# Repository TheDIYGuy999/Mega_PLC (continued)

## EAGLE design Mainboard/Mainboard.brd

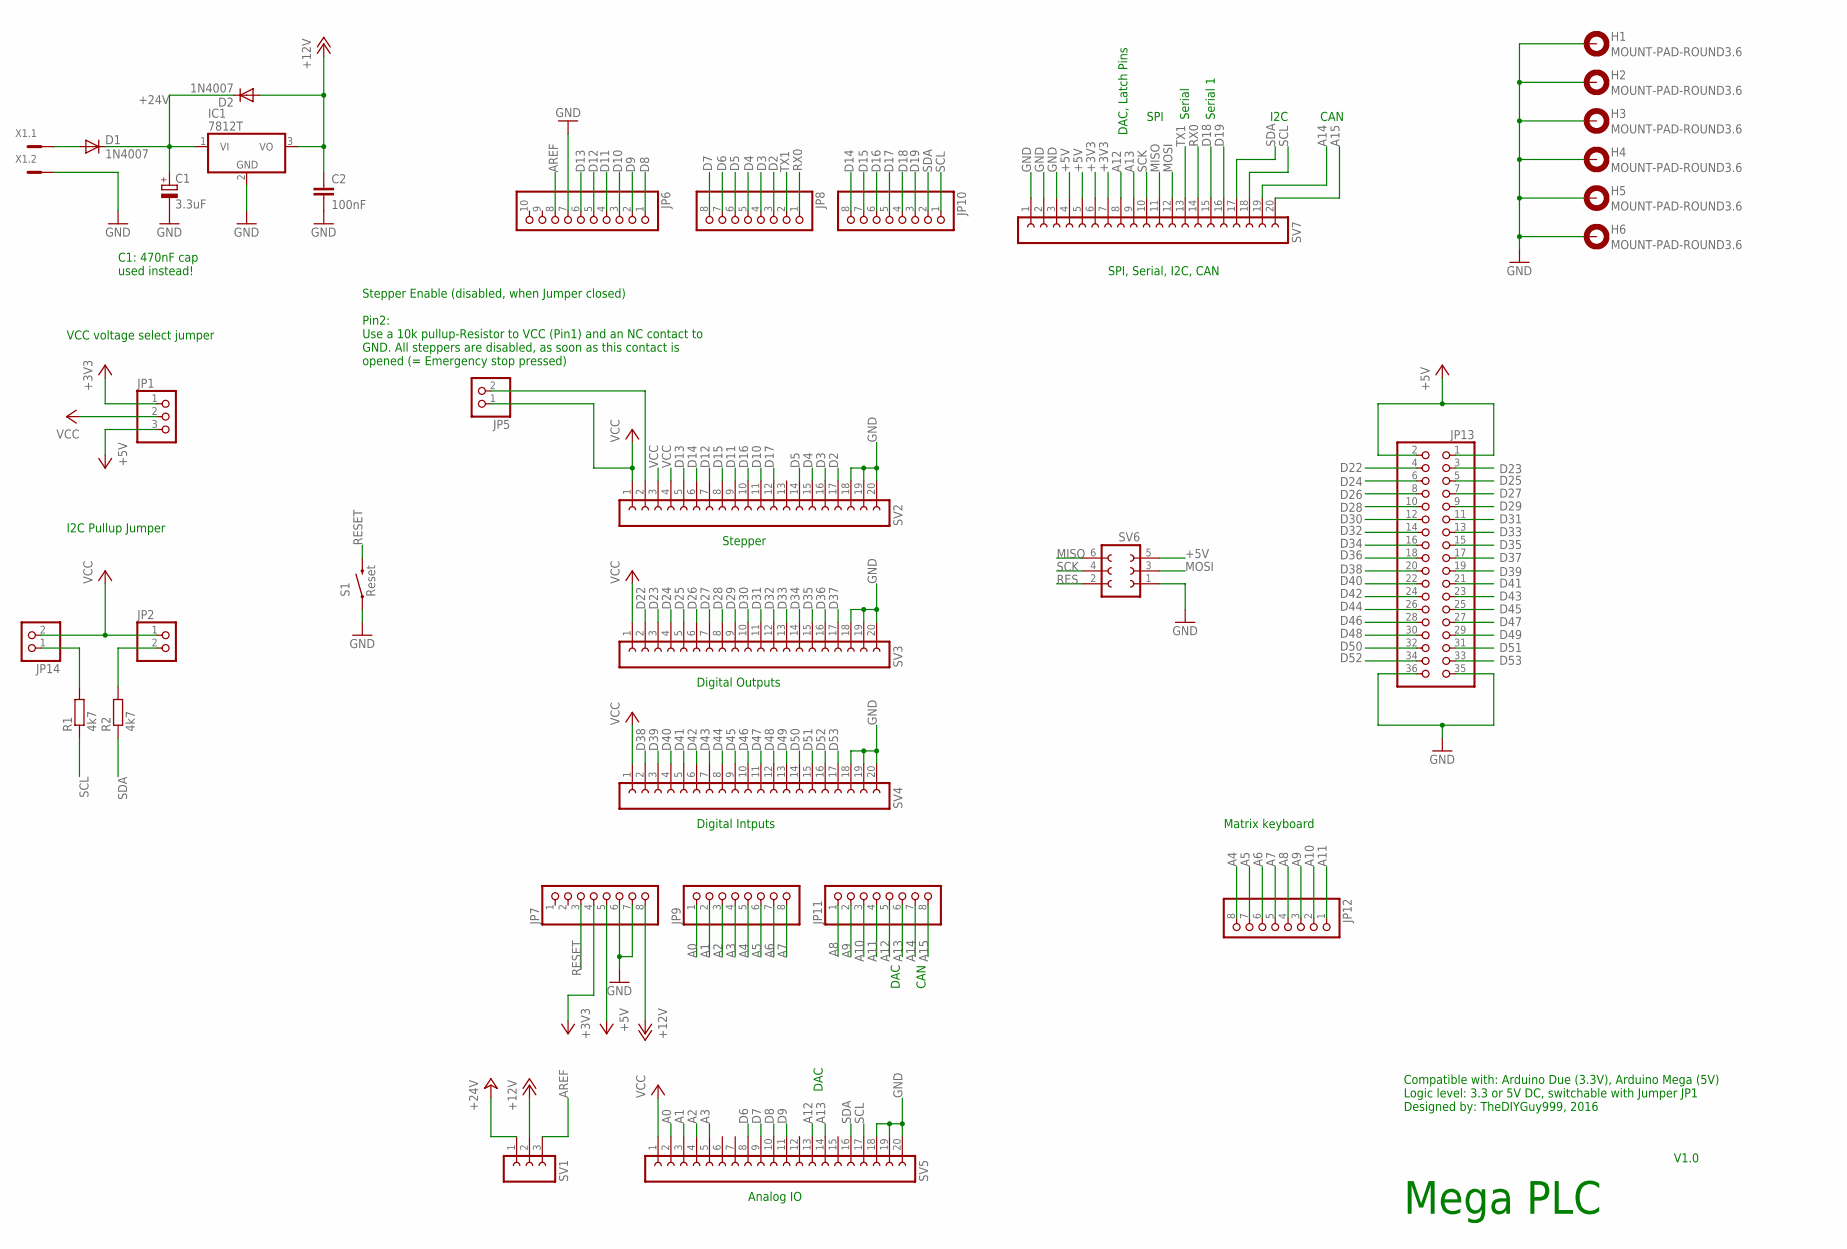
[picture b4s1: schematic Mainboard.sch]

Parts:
C1: 3.3uF; B45181A
C2: 100nF; C025-024X044
D1, D2: 1N4007; DO41-10
H1, H2, H3, H4, H5, H6: MOUNT-PAD-ROUND3.6; 3,6-PAD
IC1: 7812T; TO220H
JP1: PINHD-1X3; 1X03
JP2, JP5, JP14: PINHD-1X2; 1X02
JP6: PINHD-1X10; 1X10
JP7, JP8, JP9, JP10, JP11, JP12: PINHD-1X8; 1X08
JP13: PINHD-2X18; 2X18
R1, R2: 4k7; 0207/10
S1: Reset; TACTILE-PTH
SV1: FE03-1
SV2, SV3, SV4, SV5, SV7: FE20-1; FE20
SV6: FE03-2
X1: MC2

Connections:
+3V3: JP1.1, JP7.4, SV7.6, SV7.7
+5V: JP1.3, JP7.5, JP13.1, JP13.2, SV6.5, SV7.4, SV7.5
+12V: C2.1, D2.A, IC1.3 (VO), JP7.8, SV1.2
+24V: C1.+, D1.C, D2.C, IC1.1 (VI), SV1.1
A0: JP9.1, SV5.2
A1: JP9.2, SV5.3
A2: JP9.3, SV5.4
A3: JP9.4, SV5.5
A4: JP9.5, JP12.8
A5: JP9.6, JP12.7
A6: JP9.7, JP12.6
A7: JP9.8, JP12.5
A8: JP11.1, JP12.4
A9: JP11.2, JP12.3
A10: JP11.3, JP12.2
A11: JP11.4, JP12.1
A12: JP11.5, SV5.13, SV7.8
A13: JP11.6, SV5.14, SV7.9
A14: JP11.7, SV7.19
A15: JP11.8, SV7.20
AREF: JP6.8, SV1.3
D2: JP8.3, SV2.17
D3: JP8.4, SV2.16
D4: JP8.5, SV2.15
D5: JP8.6, SV2.14
D6: JP8.7, SV5.8
D7: JP8.8, SV5.9
D8: JP6.1, SV5.10
D9: JP6.2, SV5.11
D10: JP6.3, SV2.11
D11: JP6.4, SV2.9
D12: JP6.5, SV2.7
D13: JP6.6, SV2.5
D14: JP10.8, SV2.6
D15: JP10.7, SV2.8
D16: JP10.6, SV2.10
D17: JP10.5, SV2.12
D18: JP10.4, SV7.15
D19: JP10.3, SV7.16
D22: JP13.4, SV3.2
D23: JP13.3, SV3.3
D24: JP13.6, SV3.4
D25: JP13.5, SV3.5
D26: JP13.8, SV3.6
D27: JP13.7, SV3.7
D28: JP13.10, SV3.8
D29: JP13.9, SV3.9
D30: JP13.12, SV3.10
D31: JP13.11, SV3.11
D32: JP13.14, SV3.12
D33: JP13.13, SV3.13
D34: JP13.16, SV3.14
D35: JP13.15, SV3.15
D36: JP13.18, SV3.16
D37: JP13.17, SV3.17
D38: JP13.20, SV4.2
D39: JP13.19, SV4.3
D40: JP13.22, SV4.4
D41: JP13.21, SV4.5
D42: JP13.24, SV4.6
D43: JP13.23, SV4.7
D44: JP13.26, SV4.8
D45: JP13.25, SV4.9
D46: JP13.28, SV4.10
D47: JP13.27, SV4.11
D48: JP13.30, SV4.12
D49: JP13.29, SV4.13
D50: JP13.32, SV4.14
D51: JP13.31, SV4.15
D52: JP13.34, SV4.16
D53: JP13.33, SV4.17
GND: C1.-, C2.2, H1.B3,6, H2.B3,6, H3.B3,6, H4.B3,6, H5.B3,6, H6.B3,6, IC1.2 (GND), JP6.7, JP7.6, JP7.7, JP13.35, JP13.36, S1.1, SV2.18, SV2.19, SV2.20, SV3.18, SV3.19, SV3.20, SV4.18, SV4.19, SV4.20, SV5.18, SV5.19, SV5.20, SV6.1, SV7.1, SV7.2, SV7.3, X1.2
MISO: SV6.6, SV7.11
MOSI: SV6.3, SV7.12
unnamed: JP5.2, SV2.2
unnamed: D1.A, X1.1
RES: SV6.2
RESET: JP7.3, S1.3 (2)
RX0: JP8.1, SV7.14
SCK: SV6.4, SV7.10
SCL: JP10.1, R1.1, SV5.17, SV7.18
SCL_PULLUP: JP14.1, R1.2
SDA: JP10.2, R2.1, SV5.16, SV7.17
SDA_PULLUP: JP2.2, R2.2
TX1: JP8.2, SV7.13
VCC: JP1.2, JP2.1, JP5.1, JP14.2, SV2.1, SV2.3, SV2.4, SV3.1, SV4.1, SV5.1

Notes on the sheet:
Mega PLC
VCC voltage select jumper
I2C Pullup Jumper
Digital Outputs
Digital Intputs
Stepper
CAN
SPI, Serial, I2C, CAN
Analog IO
DAC
Matrix keyboard
I2C
Serial
Serial 1
Stepper Enable (disabled, when Jumper closed) Pin2: Use a 10k pullup-Resistor to VCC (Pin1) and an NC contact to GND. All steppers are disabled, as soon as this contact is opened (= Emergency stop pressed)
SPI
DAC, Latch Pins
V1.0
C1: 470nF cap used instead!
Compatible with: Arduino Due (3.3V), Arduino Mega (5V) Logic level: 3.3 or 5V DC, switchable with Jumper JP1 Designed by: TheDIYGuy999, 2016

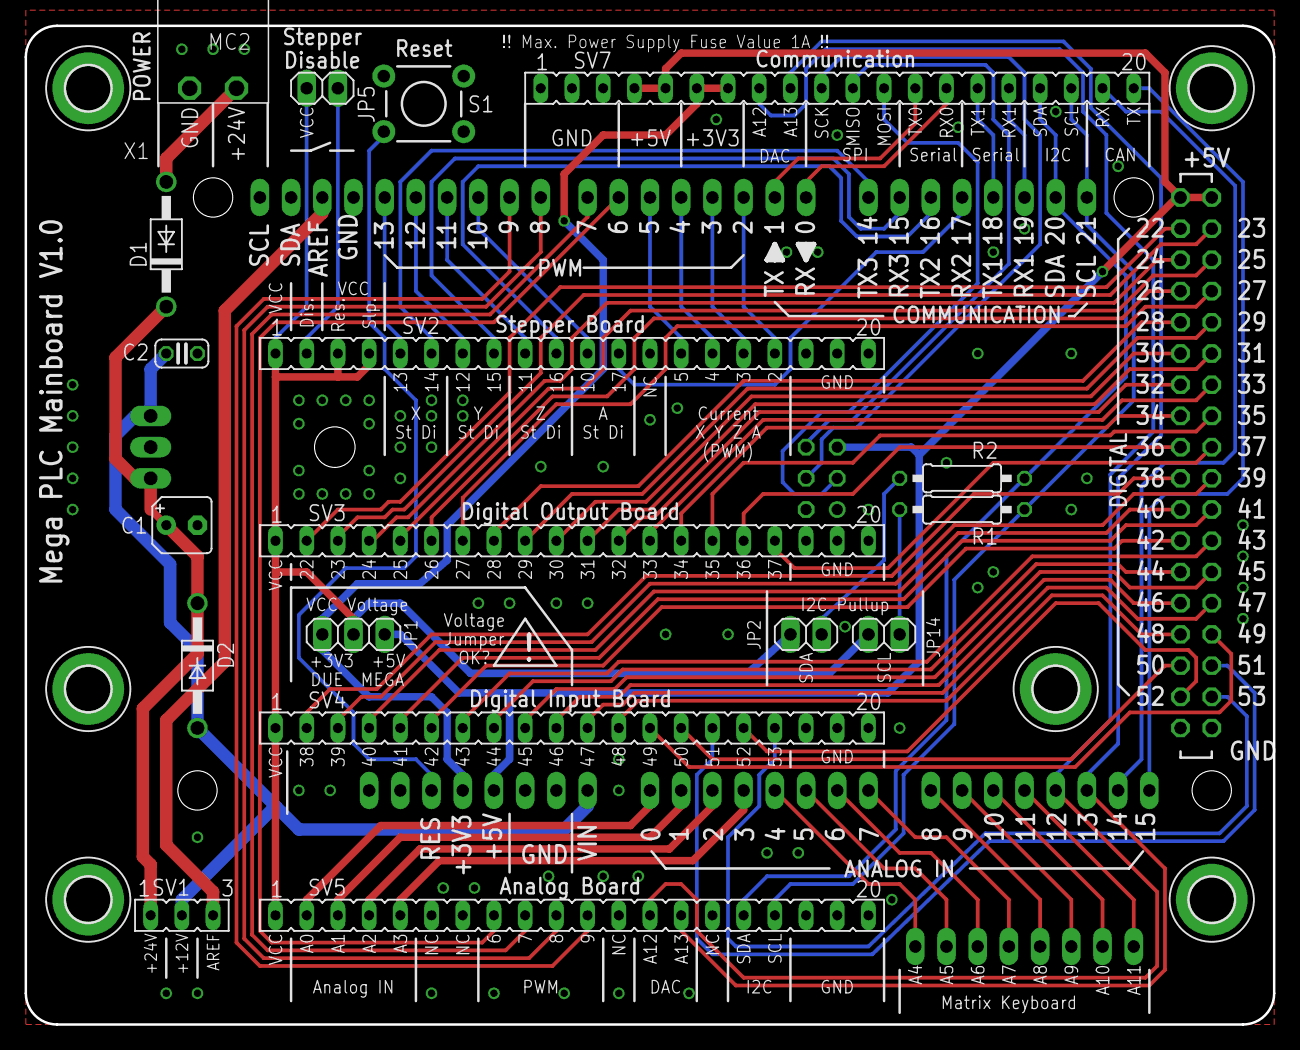
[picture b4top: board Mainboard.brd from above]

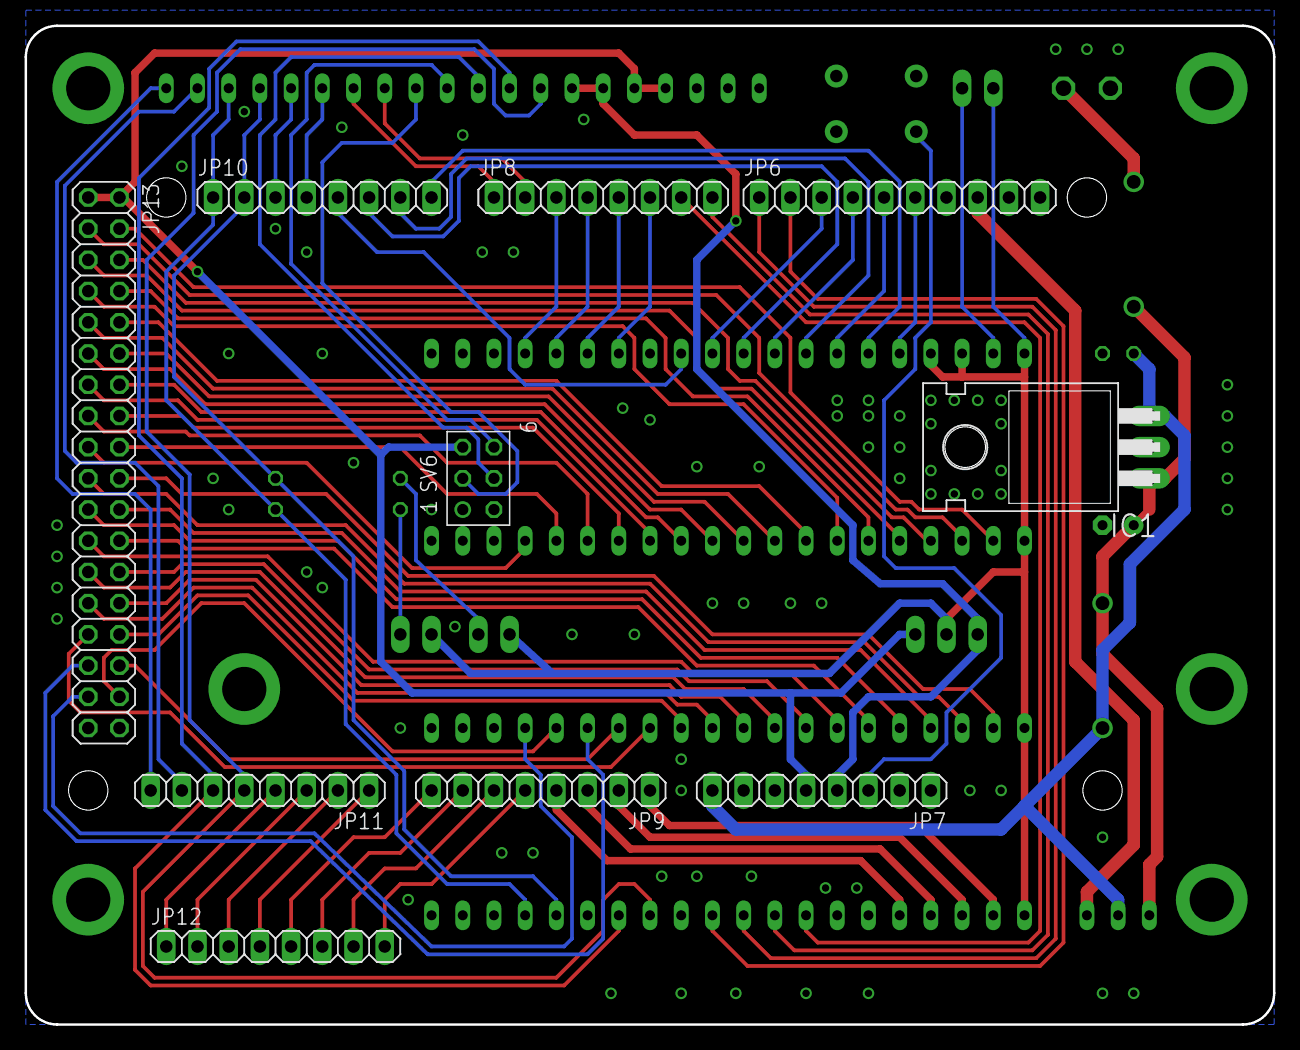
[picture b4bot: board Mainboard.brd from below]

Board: 2 copper layers, 101.6 x 81.3 mm, 34 parts (10 on the bottom side), 85 nets.

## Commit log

2017-11-12 init
2017-11-12 Pictures
2017-11-12 Initial Readme
2017-11-12 Create Digital_Input_Board
2017-11-12 Create init
2017-11-12 V1.0
2019-01-08 Create test
2019-01-08 Added application example code
